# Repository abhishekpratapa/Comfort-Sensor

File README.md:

# Comfort-Sensor

This is a walk through of designing and manufacturing a microcontroller based project. The goal is to design a consumer product.

My new product is developed from this idea. It is capable of detecting the hygine levels in any environment. Bacteria, Mold, Dust, Hydrocarbon gases. Please email me if you have any questions or are interested in ordering such a product for your family. abhishekpratapa@gmail.com

## Introduction

I've been having a bunch of headaches lately and I didn't know what the cause of those headaches was. Secondarily, during these migraines, I would notice that my mouth felt extremely parched. Initially I had thought that the cause for these symptoms was that I wasn't drinking enough water. This, however, was not the case. I was drinking more than enough of my share of water and I was still feeling horrible. I needed to do something.

I finally arrived on the conclusion that the environment around me was partially causing these symptoms. I decided to build a sensor that told me the humidity and temperature readings in my environment; it would sort of be like a comfort indicator to determine whether these headaches were caused by my surroundings.

## Prototyping

### Planning the User Experience

User Experience is most important when designing a device like this one. What do we want the user to see? Based off of the limited number of components I had available to me I opted for an analog approach in displaying the temperature and the humidity. It would sort of be like a clock. PLEASE spend more time than I did on this. You need to nail this in order to retain customers or users. The User Experience is illustrated below.

A Design Prototype

### List of Components

I began rummaging through my electronics and I managed to find a few components that I thought would be ideal to make such a device. They are listed below:

#### Components in the Prototype

- Neo Pixel Ring
- Teensy 3.1
- Battery Management Unit
- Switch
- DHT22 Humidity and Temperature Sensor
- LiPo Battery

Neo Pixel Ring

Teensy 3.1

Battery Management Unit

Switch

DHT22 Humidity and Temperature Sensor

LiPo Battery

#### Tools used to build the Prototype

- Flush Cutters
- Soldering Iron

Flush Cutters

Soldering Iron

### Planing the wiring Diagram

Below is a figure of the wiring diagram I created. It is fairly simple.

Wiring Diagram

### Wiring up the Prototype

I ended up wiring the device up before I tested it, I had run out of breadboards, and generally this is a horrible idea; however, this was not my first rodeo. I felt confident that I knew what I was doing. Everything worked out without any hiccups.

Prototype Circuit

### Writing the software

The code design is shown below in the diagram.

### Method Break Down

Translating the design to code was a fairly straight forward process. Keeping things simple in Embedded systems design means that space on the micro controller is preserved and that everything is running efficiently. 

#### Setup Method
```
/*
 * Method:  setup
 * 
 * Action:  This method is the setup loop of the program, it sets up the
 *          DHT22 and the Neopixel objects
 * 
 * params:  [None]
 *          
 * return:  void
 * 
 */
```

#### Loop Method

```
/*
 * Method:  loop
 * 
 * Action:  This method is the main loop of the program, it structurally 
 *          calls the other methods to make the program cohesive
 * 
 * params:  [None]
 *          
 * return:  void
 * 
 */
```

#### Display_correct Method

```
/*
 * Method:  display_correct
 * 
 * Action:  This method takes in two parameters, displays the correct 
 *          number of Neo_pixels and the correct color for those pixels
 * 
 * params:  value       Integer value to be displayed in the neo_pixels
 *          sent_color: Enum type color, determines the color to be displayed 
 *                      on the neo_pixels
 *          
 * return:  void
 * 
 */
```

#### Clear_previous Method

```
/*
 * Method:  clear_previous
 * 
 * Action:  This method clears the Neo_pixels and sets the values of all the Neo_pixels to zero
 * 
 * params:  [None]
 * 
 * return:  void
 * 
 */
```

#### Read_sensors Method

```
/*
 * Method:  read_sensors
 * 
 * Action:  This method reads the DHT22 and places the proper data in an int pointer array
 * 
 * params:  *data_retrieved:  This is an Integer array pointer that stores the ones, and tens 
 *                            decimal places for the temperature and the humidity values.
 *                            The first two indexes are the humidity reading and the second two 
 *                            indexes are the temperature reading in [tens, ones] format.
 * 
 * return:  void
 * 
 */
```

### Finalizing 

Here is a video of the prototype of the device

[]
(http://www.youtube.com/watch?v=CA7ydEnhpj4 "Prototype Video")

## PCB Design

Here is the Schematic Design for the project. (Click on it to go to the PDF of the schematic)

[]
(https://github.com/abhishekpratapa/Comfort-Sensor/blob/master/Comfort_Sensor_PCB/comfort_board.pdf "PDF Schematic")

Here is the PCB design for the project.

Please take a look at the eagle CAD and schematic designs in: https://github.com/abhishekpratapa/Comfort-Sensor/tree/master/Comfort_Sensor_PCB

Here is a rendering of the Circuit in Solidworks

## Financing

### Low Volume

#### Components

| Name of Component | Quantity | Supplier | Price | Shipping | URL |
|    :---     |     :---:      |     :---:      |     :---:     | :---: | :--- |
| ATMega328  | 1 | Mouser | $3.70 | $4.70 | http://www.mouser.com/ProductDetail/Atmel/ATMEGA328P-PU/?qs=K8BHR703ZXguOQv3sKbWcg%3D%3D&gclid=CNLnypKQ488CFQEJaQodVeQNbA |
| Crystal 16MHz | 1 | Mouser | $0.36 | $-.--  | http://www.mouser.com/ProductDetail/CTS/ATS16B-E/?qs=tjlMjqRIEYTG8fmTS%252b7FfQ%3D%3D&gclid=CMWL4dOQ488CFQipaQodB0oNbg |
| DHT22  | 1 | Ebay | $3.70 | $-.-- | http://www.ebay.com/itm/New-DHT22-AM2302-Digital-Temperature-Humidity-Sensor-Replace-SHT11-SHT15-Arduino/162147611172 |
| Mini-Pushbutton | 1 | Sparkfun | $0.35 | $2.35  | https://www.sparkfun.com/products/97 |
| Neo-Pixel Ring | 1 | Adafruit | $7.50 | $4.75  | https://www.adafruit.com/products/1643?gclid=CMuP2r6R5c8CFYE2aQodMi0GSg |
| USB Mini B | 1 | Mouser | $0.76 | $1.25  | http://www.mouser.com/ProductDetail/CUI/UJ2-MBH-1-SMT/?qs=sGAEpiMZZMulM8LPOQ%252byk%252br6FietFiXBYOK8b9%2fsuNIy0pbKqeLWLA%3d%3d |
| LiPo 3.7V battery pack | 1 | Mouser | $13.68 | $4.25  | http://www.mouser.com/ProductDetail/Renata/ICP402025PC-1/?qs=WtvvTbtNXq%252bQv7inF4n3oA%3d%3d |
| JST-Connector | 1 | Mouser | $0.95 | $-.--  | https://www.sparkfun.com/products/9749 |
| 0805 LED | 1 | DigiKey | $0.50 | $4.58  | http://www.digikey.com/product-detail/en/kingbright/APT2012SECK-J3-PRV/754-1791-1-ND/4753616 |
| Surface Mount Right Angle Switch | 1 | SparkFun | $0.48 |  $-.--  | https://www.sparkfun.com/products/10860 |
| Battery Management Chip | 1 | Mouser | $0.94 |  $-.--  | http://www.mouser.com/ProductDetail/Microchip-Technology/MCP73833T-AMI-MF/?qs=Fxu3fLyJv8epbqy6GsGQQA%3D%3D |
| JST 3-pin  | 1 | SparkFun | $1.50 |  $-.--  | https://www.sparkfun.com/products/9915 |
| 10K Resistor 1206 | 2 | Mouser | $0.19 |  $-.--  | http://www.mouser.com/ProductDetail/ROHM-Semiconductor/KTR18EZPF1002/?qs=sGAEpiMZZMvdGkrng054t4QdAY%2fQ0LweN2wTdK7f9y4%3d |
| 150 Ohm Resistor 0805 | 1 | Mouser | $0.10 |  $-.--  | http://www.mouser.com/ProductDetail/ROHM-Semiconductor/ESR10EZPJ151/?qs=sGAEpiMZZMvdGkrng054t4QdAY%2fQ0Lwe25OmOs7YyvE%3d |
| 1 kOhm Resistor 0805 | 1 | Mouser | $0.15 |  $-.--  | http://www.mouser.com/ProductDetail/ROHM-Semiconductor/ESR10EZPF1001/?qs=sGAEpiMZZMvdGkrng054t4QdAY%2fQ0LwesgDXVtvvnU8%3d |
| 10 kOhm Resistor 0805 | 2 | Mouser | $0.17 |  $-.--  | http://www.mouser.com/ProductDetail/ROHM-Semiconductor/KTR10EZPF1002/?qs=sGAEpiMZZMvdGkrng054t4QdAY%2fQ0LweGk5BfWf21pU%3d |
| 150 kOhm Resistor 0805 | 1 | Mouser | $0.15 |  $-.--  | http://www.mouser.com/ProductDetail/ROHM-Semiconductor/ESR10EZPF1503/?qs=sGAEpiMZZMvdGkrng054t4QdAY%2fQ0Lwe41fW0x%2fX95k%3d |
| 22pF Capicator 1206 | 2 | Mouser | $0.10 |  $-.--  | http://www.mouser.com/ProductDetail/Vishay-Vitramon/VJ1206A220JXJCW1BC/?qs=sGAEpiMZZMs0AnBnWHyRQAR7at33PD0%252bkVtEu2CEPmo%3d |
| 10pF Capicator 0805 | 2 | Mouser | $0.10 |  $-.--  | http://www.mouser.com/ProductDetail/AVX/0805YD106KAT2A/?qs=dV90weSEKCml0j81AJ8E6Q%3D%3D |

#### PCB Cost

| Quantity | Supplier | Price | Shipping |
|    :---     |     :---:      |     :---:      |     :---:     |
| 3 | Osh Park | $23.50 | $12.50 |
| 40 | Osh Park | $188.00 | $12.50 |

#### Consumables

| Name of Consumable | Quantity | Supplier | Price | Shipping | URL |
|   :---   |    :---     |     :---:      |     :---:      |     :---:     | :--- |
| Solder Paste | 3 | Digi-Key | $23.50 | $4.89 | http://www.digikey.com/product-detail/en/SMD291AX/SMD291AX-ND/1160002 |

#### Housing Costs

#### Manufacturing Costs

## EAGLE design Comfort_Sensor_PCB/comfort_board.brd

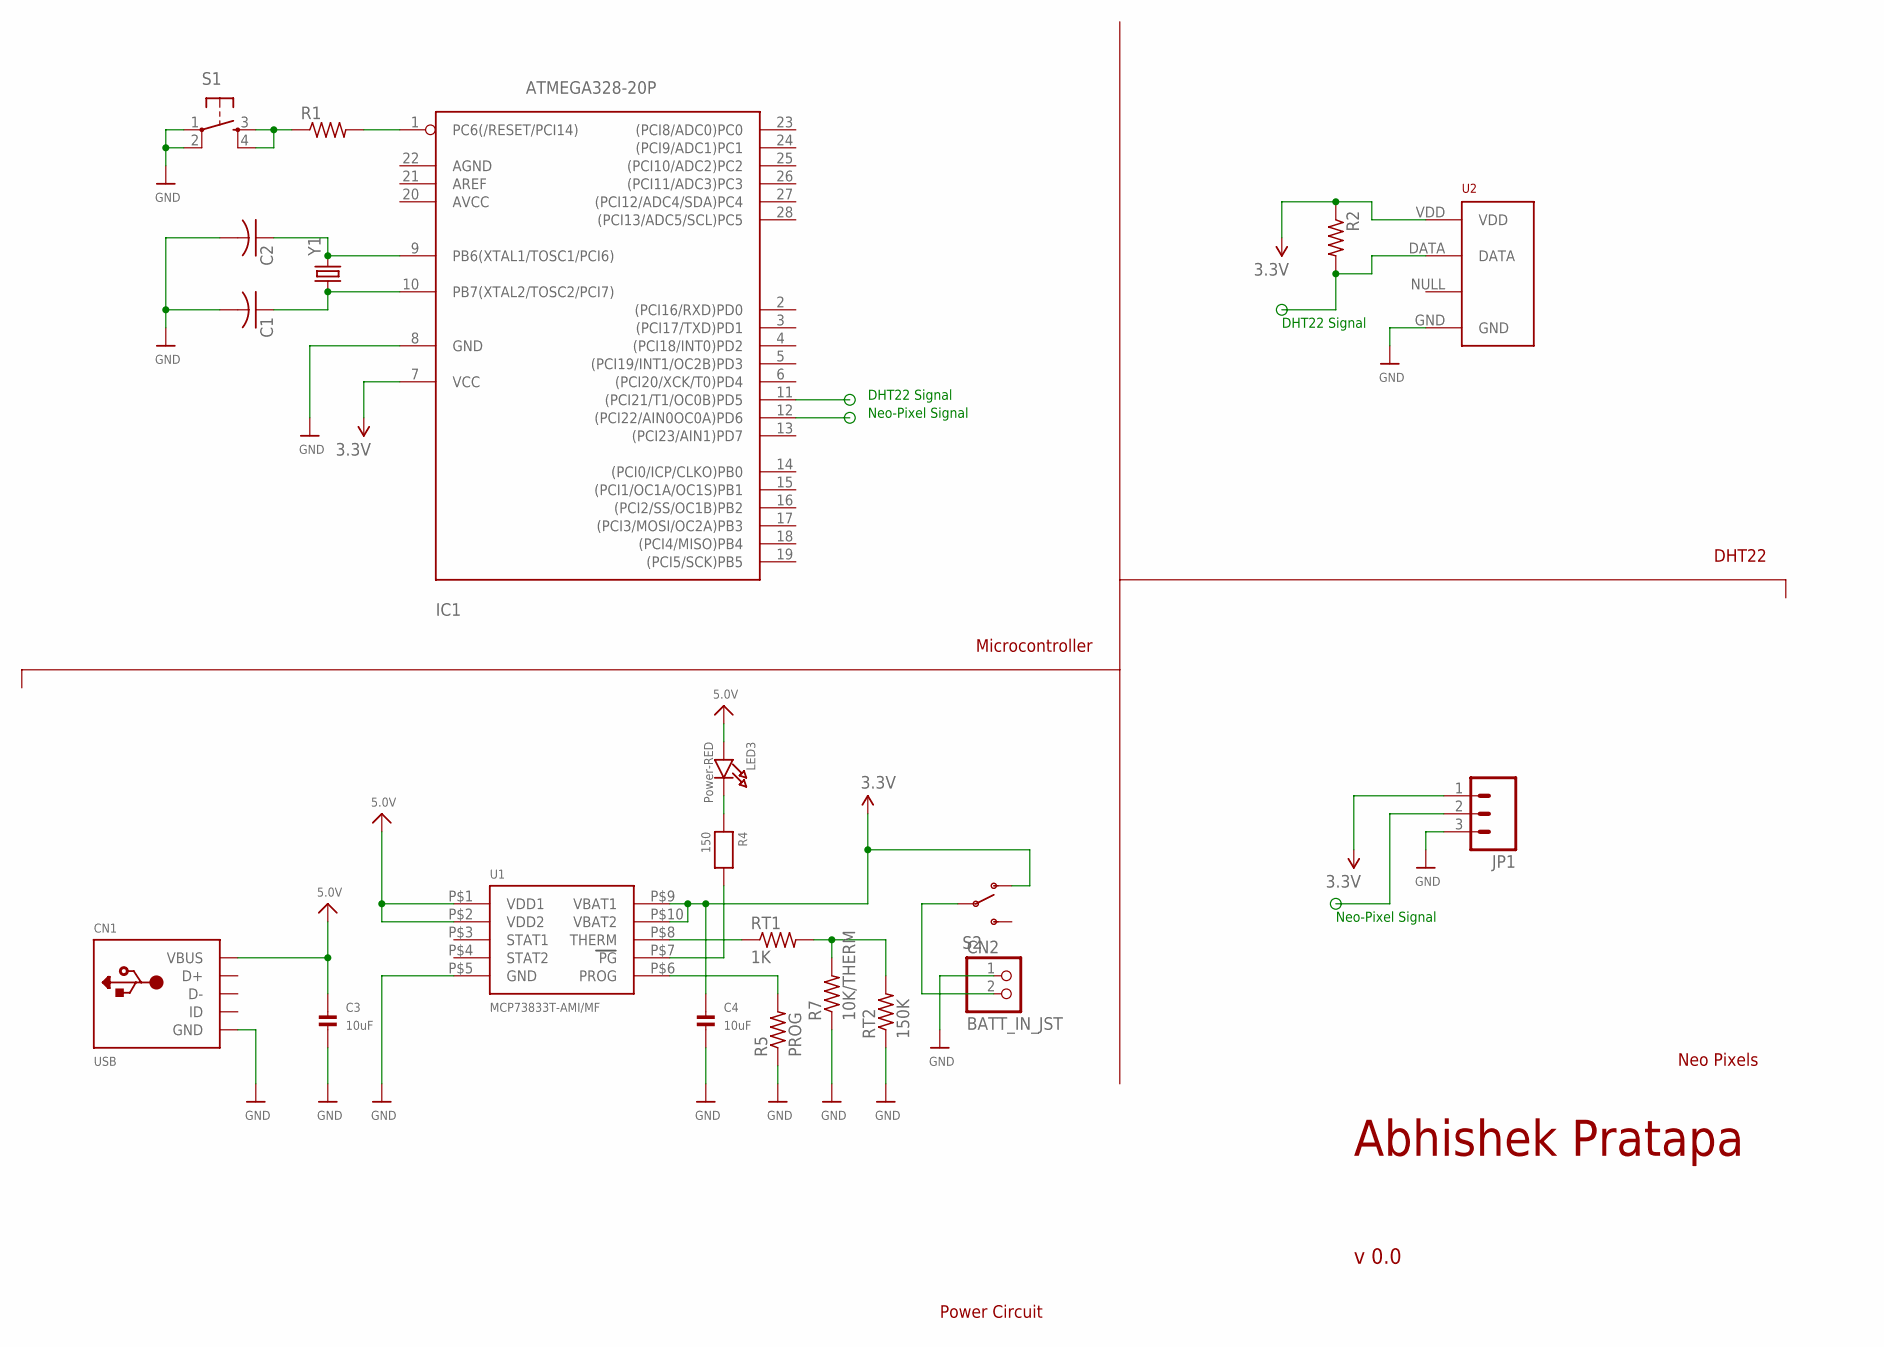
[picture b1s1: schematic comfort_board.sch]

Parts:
C1, C2: C-USC1206; C1206
C3, C4: 10uF; 0805
CN1: USB; USB-MINIB_LARGER
CN2: BATT_IN_JST; JSTPH2
IC1: ATMEGA328-20P; DIL28-3
JP1: M03PTH; 1X03
LED3: Power-RED; CHIPLED_0805
R1, R2: R-US_M1206; M1206
R4: 150; 0805
R5: PROG; 0805-THM
R7: 10K/THERM; 0805-THM
RT1: 1K; R0805
RT2: 150K; R0805
S1: TAC_SWITCHPTH; TACTILE-PTH
S2: SWITCH-SPSTSMD2; SWITCH-SPDT-SMD
U1: MCP73833T-AMI/MF; DFN10_3X3MM
U2: RHT03_DHT-22_AM2302RA; RHT03_DHT-22/RA
Y1: CRYSTALHC49US; HC49US

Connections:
3.3V: C4.1, IC1.7 (VCC), JP1.1, R2.1, S2.1 (O), U1.P$9 (VBAT1), U1.P$10 (VBAT2), U2.VDD
5.0V: C3.1, CN1.VBUS, LED3.A, U1.P$1 (VDD1), U1.P$2 (VDD2)
DHT22: IC1.11 ((PCI21/T1/OC0B)PD5), R2.2, U2.DATA
GND: C1.2, C2.2, C3.2, C4.2, CN1.GND, CN2.1, IC1.8 (GND), JP1.3, R5.1, R7.1, RT2.1, S1.1, S1.2, U1.P$5 (GND), U2.GND
unnamed: C2.1, IC1.9 (PB6(XTAL1/TOSC1/PCI6)), Y1.2
unnamed: C1.1, IC1.10 (PB7(XTAL2/TOSC2/PCI7)), Y1.1
unnamed: R1.1, S1.3, S1.4
unnamed: IC1.1 (PC6(/RESET/PCI14)), R1.2
unnamed: IC1.12 ((PCI22/AIN0OC0A)PD6), JP1.2
unnamed: CN2.2, S2.2
unnamed: R4.2, U1.P$7 (PG)
unnamed: RT1.1, U1.P$8 (THERM)
unnamed: R7.2, RT1.2, RT2.2
unnamed: LED3.C, R4.1
unnamed: R5.2, U1.P$6 (PROG)

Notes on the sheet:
DHT22 Signal
Neo-Pixel Signal
Microcontroller
DHT22
Neo Pixels
Power Circuit
Abhishek Pratapa
v 0.0

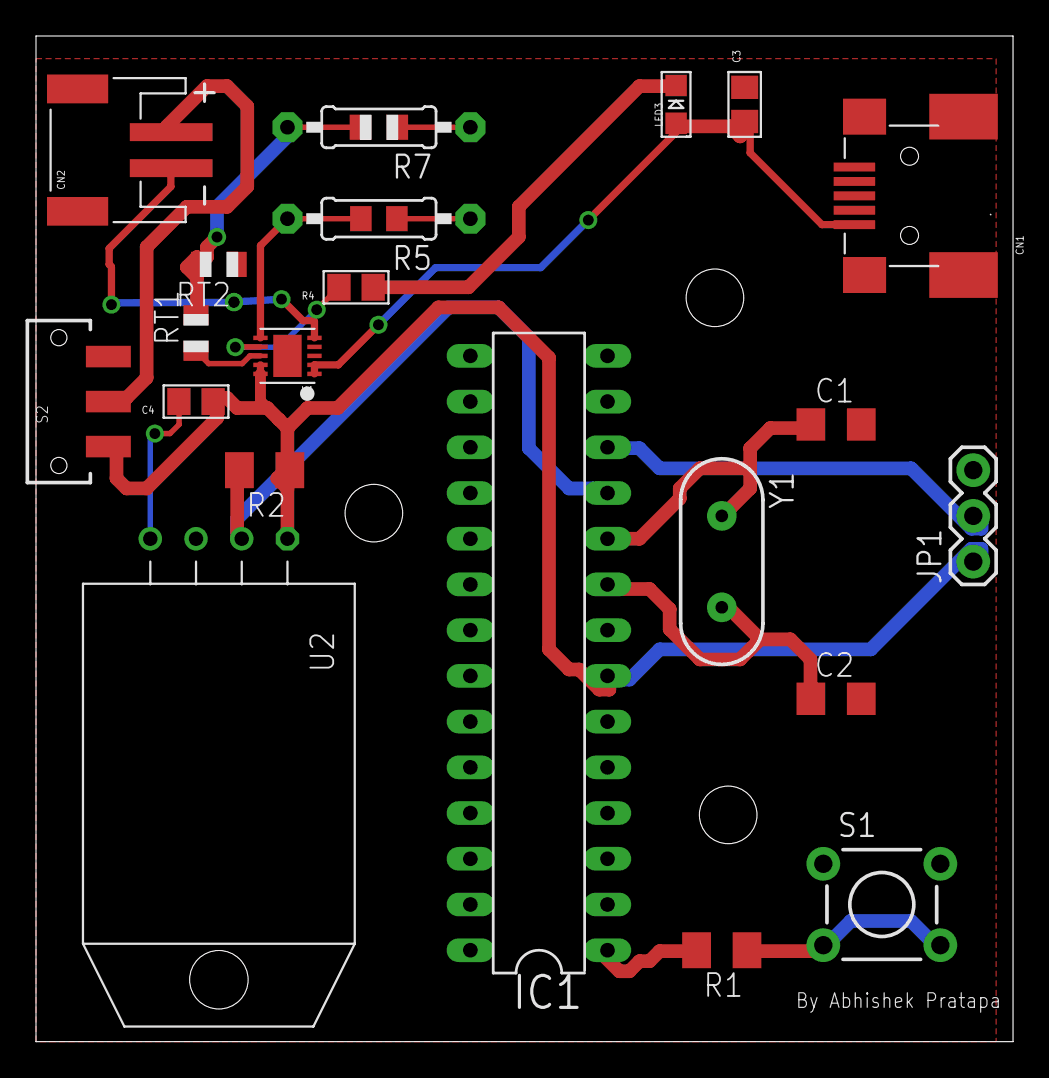
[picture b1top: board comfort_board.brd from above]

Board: 2 copper layers, 54.3 x 55.9 mm, 21 parts (0 on the bottom side), 15 nets.

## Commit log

2016-10-17 Arduino Sensor code
2016-10-17 project schedule
2016-10-17 Linked up DHT sensor to the Arduino code
2016-10-17 Project Scope
2016-10-17 Updated Gantt Chart
2016-10-17 updated arduino code
2016-10-17 added images
2016-10-17 The main commit
2016-10-17 Added a youtube video of the device
2016-10-17 added a total image
2016-10-17 Added the diagrams
2016-10-17 updated method code
2016-10-17 fixed a documentation error in the code
2016-10-17 Updated the code
2016-10-17 many PCB designs
2016-10-17 Progress
2016-10-17 Updated timeline
2016-10-18 added image
2016-10-18 Eagle cad
2016-10-18 Table
2016-10-18 spacing issues table
2016-10-18 Added more components for the PCB
2016-10-18 Added all parts to the sensor
2016-10-18 Updated URLS
2016-10-18 Updates to the Table
2016-10-18 Updated the finance section
2016-10-18 Updated the description
2016-10-19 added solidworks file

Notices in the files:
parts and their libraries:
SparkFun-FreqCtrl: Licensing: Creative Commons ShareAlike 4.0 International - https://creativecommons.org/licenses/by-sa/4.0
